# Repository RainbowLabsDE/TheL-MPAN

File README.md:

# TheLÄMPAN
Für so ne Lampe von IKEA ein Custom PCB

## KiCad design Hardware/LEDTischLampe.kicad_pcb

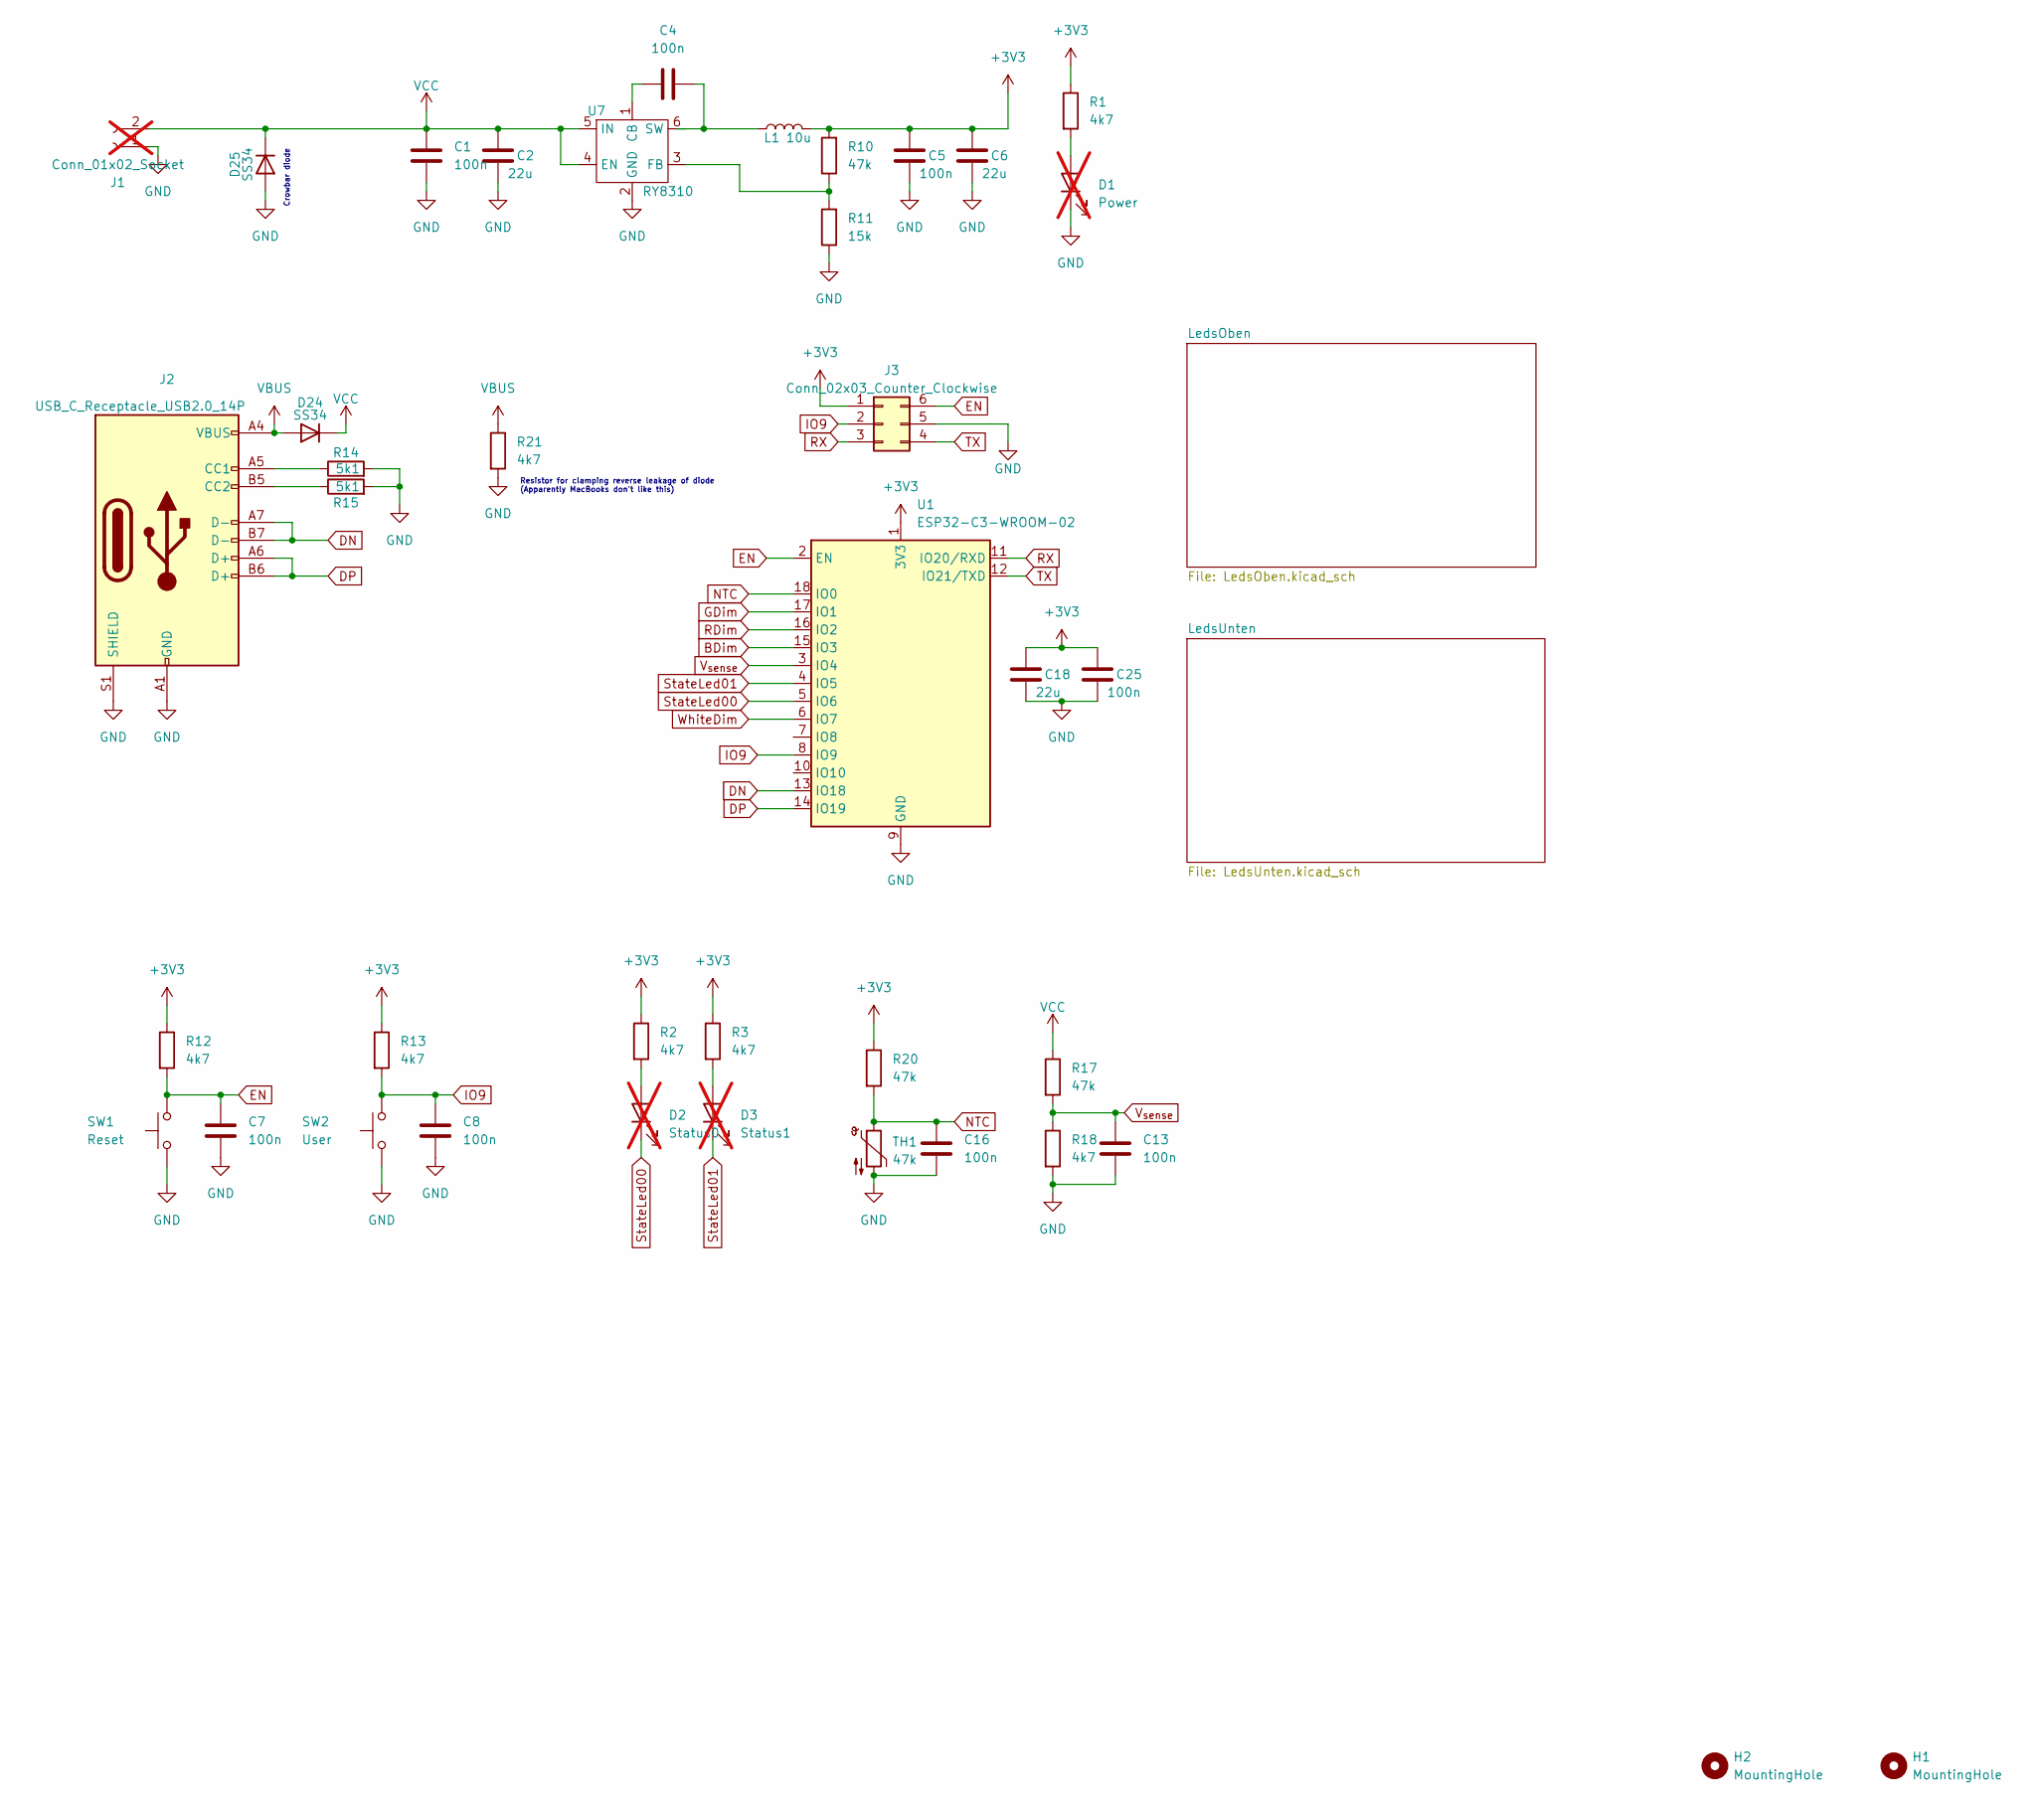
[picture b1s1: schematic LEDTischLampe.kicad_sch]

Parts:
C1, C4, C5, C7, C8, C13, C16, C25: 100n; C_0402_1005Metric
C2, C6, C18: 22u; C_0805_2012Metric
D1: Power; LED_0805_2012Metric; not fitted
D2: Status0; LED_0805_2012Metric; not fitted
D3: Status1; LED_0805_2012Metric; not fitted
D24, D25: SS34; D_SMA
H1, H2: MountingHole; MountingHole_3.2mm_M3
J1: Conn_01x02_Socket; TerminalBlock_Phoenix_PT-1,5-2-5.0-H_1x02_P5.00mm_Horizontal; not fitted
J2: USB_C_Receptacle_USB2.0_14P; USB-C_SMD-TYPE-C-31-M-12
J3: Conn_02x03_Counter_Clockwise; Tag-Connect_TC2030-IDC-NL_2x03_P1.27mm_Vertical
L1: 10u; IND-SMD_L2.5-W2.0
R1, R2, R3, R12, R13, R18, R21: 4k7; R_0402_1005Metric
R10, R17, R20: 47k; R_0402_1005Metric
R11: 15k; R_0402_1005Metric
R14, R15: 5k1; R_0402_1005Metric
SW1: Reset; SW_SPST_TL3342
SW2: User; SW_SPST_TL3342
TH1: 47k; R_0402_1005Metric
U1: ESP32-C3-WROOM-02
U7: RY8310; SOT-23-6

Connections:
+3V3: C5.1, C6.1, C18.1, C25.1, J3.1, L1.2, R1.1, R2.1, R3.1, R10.2, R12.1, R13.1, R20.1, U1.1 (3V3)
BDim: U1.15 (IO3); also elsewhere on the board
DN: J2.A7 (D-), J2.B7 (D-), U1.13 (IO18)
DP: J2.A6 (D+), J2.B6 (D+), U1.14 (IO19)
EN: C7.1, J3.6, R12.2, SW1.2, U1.2 (EN)
GDim: U1.17 (IO1); also elsewhere on the board
GND: C1.2, C2.2, C5.2, C6.2, C7.2, C8.2, C13.2, C16.2, C18.2, C25.2, D1.1 (K), D25.2 (A), J1.1, J2.A1 (GND), J2.A12 (GND), J2.B1 (GND), J2.B12 (GND), J2.S1 (SHIELD), J3.5, R11.1, R14.2, R15.2, R18.2, R21.2, SW1.1, SW2.1, TH1.2, U1.9 (GND), U1.19 (GND), U7.2 (GND); also elsewhere on the board
IO9: C8.1, J3.2, R13.2, SW2.2, U1.8 (IO9)
NTC: C16.1, R20.2, TH1.1, U1.18 (IO0)
unnamed: C4.2, L1.1
unnamed: D1.2 (A), R1.2
unnamed: D2.2 (A), R2.2
unnamed: D3.2 (A), R3.2
unnamed: J2.A5 (CC1), R14.1
unnamed: J2.B5 (CC2), R15.1
unnamed: C4.1, U7.1 (CB)
unnamed: R10.1, R11.2, U7.3 (FB)
RDim: U1.16 (IO2); also elsewhere on the board
RX: J3.3, U1.11 (IO20/RXD)
StateLed00: D2.1 (K), U1.5 (IO6)
StateLed01: D3.1 (K), U1.4 (IO5)
TX: J3.4, U1.12 (IO21/TXD)
VBUS: D24.2 (A), J2.A4 (VBUS), J2.A9 (VBUS), J2.B4 (VBUS), J2.B9 (VBUS), R21.1
VCC: C1.1, C2.1, D24.1 (K), D25.1 (K), J1.2, R17.1, U7.4 (EN), U7.5 (IN); also elsewhere on the board
V_{sense}: C13.1, R17.2, R18.1, U1.3 (IO4)
WhiteDim: U1.6 (IO7); also elsewhere on the board

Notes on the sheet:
Crowbar diode
Resistor for clamping reverse leakage of diode (Apparently MacBooks don't like this)

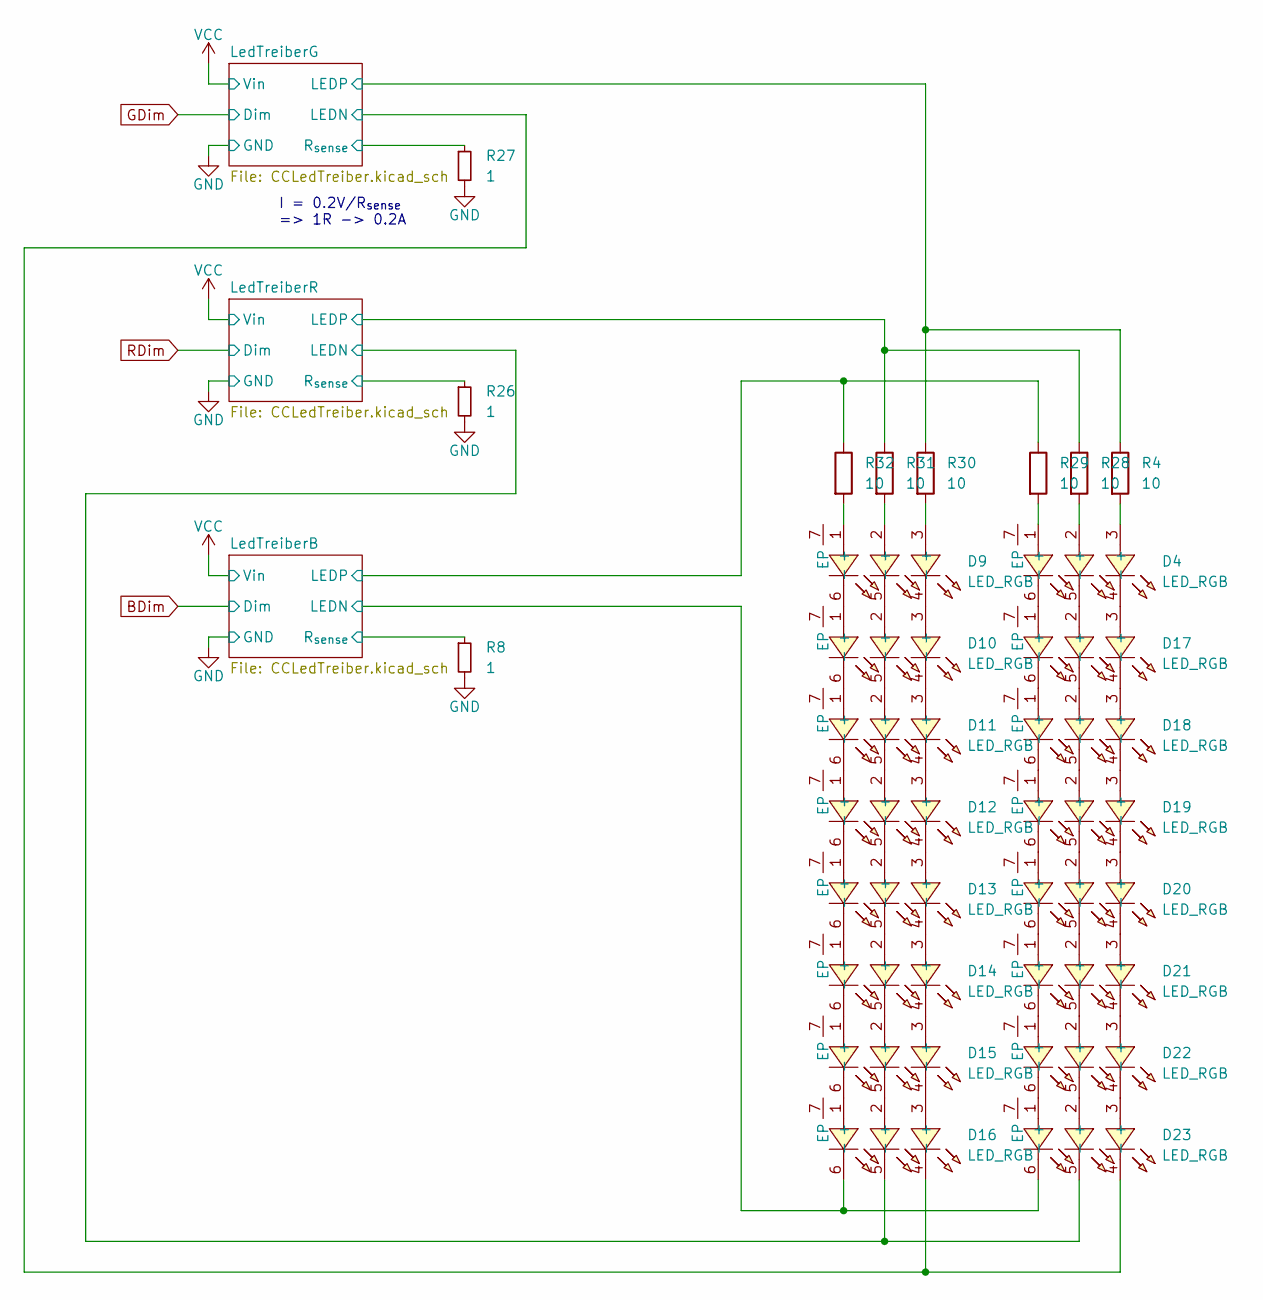
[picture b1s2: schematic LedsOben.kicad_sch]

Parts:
D4, D9, D10, D11, D12, D13, D14, D15, D16, D17, D18, D19, D20, D21, D22, D23: LED_RGB; LED-SMD_6P-L5.0-W5.0-BL_TC5053RGBE60
R4, R28, R29, R30, R31, R32: 10; R_0805_2012Metric
R8, R26, R27: 1; R_0805_2012Metric

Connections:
/LedsOben/LedTreiberB/LEDN: D16.6 (-), D23.6 (-), R8.1; also elsewhere on the board
/LedsOben/LedTreiberB/LEDP: R29.1, R32.1; also elsewhere on the board
/LedsOben/LedTreiberG/LEDN: D16.4 (-), D23.4 (-), R27.1; also elsewhere on the board
/LedsOben/LedTreiberG/LEDP: R4.1, R30.1; also elsewhere on the board
/LedsOben/LedTreiberR/LEDN: D16.5 (-), D23.5 (-), R26.1; also elsewhere on the board
/LedsOben/LedTreiberR/LEDP: R28.1, R31.1; also elsewhere on the board
GND: R8.2, R26.2, R27.2; also elsewhere on the board
unnamed: D4.1 (+), R29.2
unnamed: D4.2 (+), R28.2
unnamed: D4.3 (+), R4.2
unnamed: D9.1 (+), R32.2
unnamed: D9.2 (+), R31.2
unnamed: D9.3 (+), R30.2
unnamed: D9.6 (-), D10.1 (+)
unnamed: D9.5 (-), D10.2 (+)
unnamed: D9.4 (-), D10.3 (+)
unnamed: D10.4 (-), D11.3 (+)
unnamed: D10.5 (-), D11.2 (+)
unnamed: D10.6 (-), D11.1 (+)
unnamed: D11.4 (-), D12.3 (+)
unnamed: D11.5 (-), D12.2 (+)
unnamed: D11.6 (-), D12.1 (+)
unnamed: D12.4 (-), D13.3 (+)
unnamed: D12.5 (-), D13.2 (+)
unnamed: D12.6 (-), D13.1 (+)
unnamed: D13.4 (-), D14.3 (+)
unnamed: D13.5 (-), D14.2 (+)
unnamed: D13.6 (-), D14.1 (+)
unnamed: D14.4 (-), D15.3 (+)
unnamed: D14.5 (-), D15.2 (+)
unnamed: D14.6 (-), D15.1 (+)
unnamed: D15.4 (-), D16.3 (+)
unnamed: D15.5 (-), D16.2 (+)
unnamed: D15.6 (-), D16.1 (+)
unnamed: D4.6 (-), D17.1 (+)
unnamed: D4.5 (-), D17.2 (+)
unnamed: D4.4 (-), D17.3 (+)
unnamed: D17.4 (-), D18.3 (+)
unnamed: D17.5 (-), D18.2 (+)
unnamed: D17.6 (-), D18.1 (+)
unnamed: D18.4 (-), D19.3 (+)
unnamed: D18.5 (-), D19.2 (+)
unnamed: D18.6 (-), D19.1 (+)
unnamed: D19.4 (-), D20.3 (+)
unnamed: D19.5 (-), D20.2 (+)
unnamed: D19.6 (-), D20.1 (+)
unnamed: D20.4 (-), D21.3 (+)
unnamed: D20.5 (-), D21.2 (+)
unnamed: D20.6 (-), D21.1 (+)
unnamed: D21.4 (-), D22.3 (+)
unnamed: D21.5 (-), D22.2 (+)
unnamed: D21.6 (-), D22.1 (+)
unnamed: D22.4 (-), D23.3 (+)
unnamed: D22.5 (-), D23.2 (+)
unnamed: D22.6 (-), D23.1 (+)

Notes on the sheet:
I = 0.2V/R_{sense} => 1R -> 0.2A

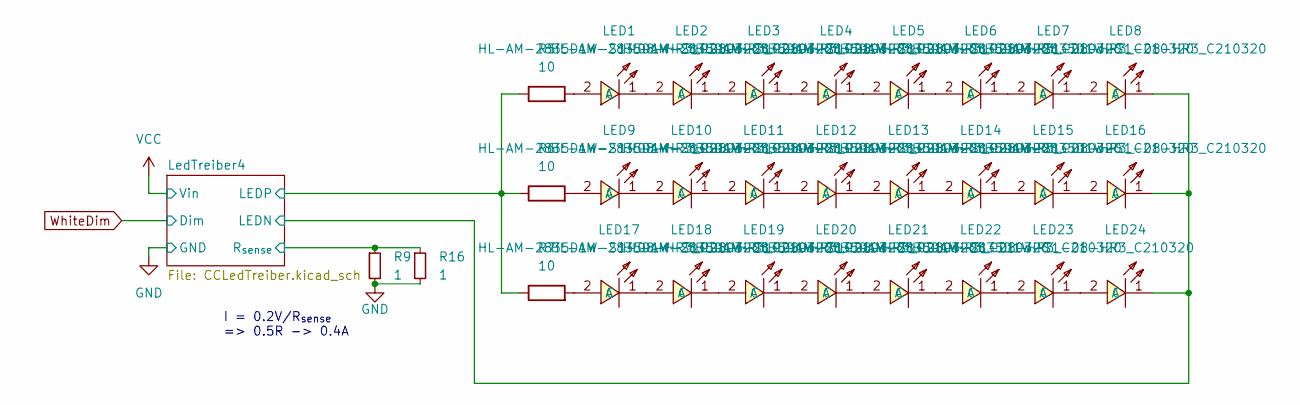
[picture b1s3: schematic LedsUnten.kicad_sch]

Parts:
LED1, LED2, LED3, LED4, LED5, LED6, LED7, LED8, LED9, LED10, LED11, LED12, LED13, LED14, LED15, LED16, LED17, LED18, LED19, LED20, LED21, LED22, LED23, LED24: HL-AM-2835D1W-S1-08-HR3_C210320; LED-SMD_L3.3-W2.8-RD
R5, R6, R7: 10; R_0805_2012Metric
R9, R16: 1; R_0805_2012Metric

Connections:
/LedsUnten/LedTreiber4/LEDN: LED8.1 (C), LED16.1 (C), LED24.1 (C), R9.1, R16.1; also elsewhere on the board
/LedsUnten/LedTreiber4/LEDP: R5.1, R6.1, R7.1; also elsewhere on the board
GND: R9.2, R16.2; also elsewhere on the board
unnamed: LED1.2 (A), R5.2
unnamed: LED1.1 (C), LED2.2 (A)
unnamed: LED2.1 (C), LED3.2 (A)
unnamed: LED3.1 (C), LED4.2 (A)
unnamed: LED4.1 (C), LED5.2 (A)
unnamed: LED5.1 (C), LED6.2 (A)
unnamed: LED6.1 (C), LED7.2 (A)
unnamed: LED7.1 (C), LED8.2 (A)
unnamed: LED9.2 (A), R6.2
unnamed: LED9.1 (C), LED10.2 (A)
unnamed: LED10.1 (C), LED11.2 (A)
unnamed: LED11.1 (C), LED12.2 (A)
unnamed: LED12.1 (C), LED13.2 (A)
unnamed: LED13.1 (C), LED14.2 (A)
unnamed: LED14.1 (C), LED15.2 (A)
unnamed: LED15.1 (C), LED16.2 (A)
unnamed: LED17.2 (A), R7.2
unnamed: LED17.1 (C), LED18.2 (A)
unnamed: LED18.1 (C), LED19.2 (A)
unnamed: LED19.1 (C), LED20.2 (A)
unnamed: LED20.1 (C), LED21.2 (A)
unnamed: LED21.1 (C), LED22.2 (A)
unnamed: LED22.1 (C), LED23.2 (A)
unnamed: LED23.1 (C), LED24.2 (A)

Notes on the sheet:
I = 0.2V/R_{sense} => 0.5R -> 0.4A

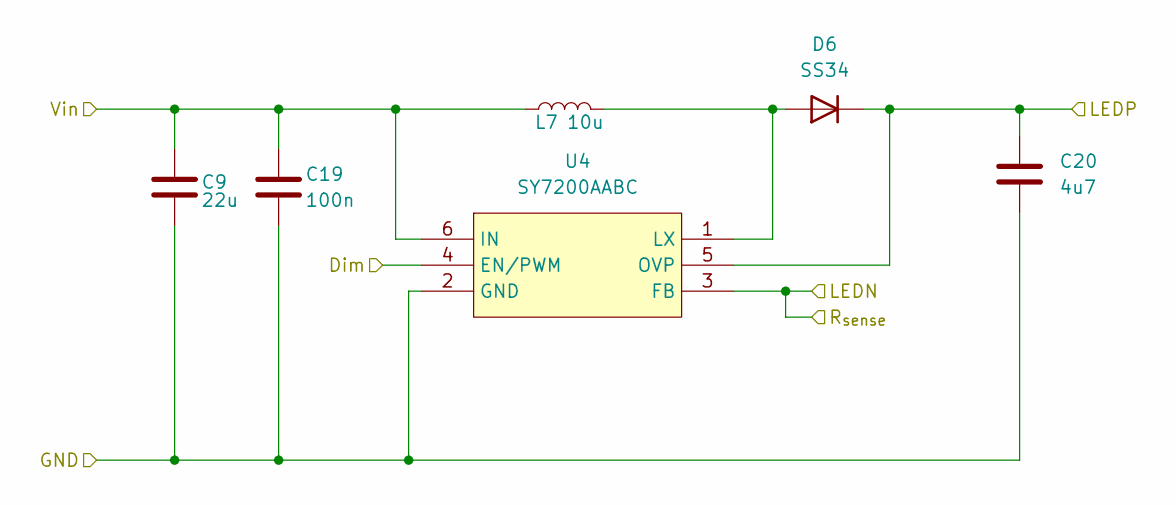
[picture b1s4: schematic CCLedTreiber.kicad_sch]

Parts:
C9: 22u; C_0805_2012Metric
C19: 100n; C_0402_1005Metric
C20: 4u7; C_1206_3216Metric
D6: SS34; D_SMA
L7: 10u; IND-SMD_L2.5-W2.0
U4: SY7200AABC; SOT-23-6_L2.9-W1.6-P0.95-LS2.8-BR

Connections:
/LedsOben/LedTreiberB/LEDN: U4.3 (FB); also elsewhere on the board
/LedsOben/LedTreiberB/LEDP: C20.1, D6.1 (K), U4.5 (OVP); also elsewhere on the board
BDim: U4.4 (EN/PWM); also elsewhere on the board
GND: C9.2, C19.2, C20.2, U4.2 (GND); also elsewhere on the board
unnamed: D6.2 (A), L7.2, U4.1 (LX)
VCC: C9.1, C19.1, L7.1, U4.6 (IN); also elsewhere on the board

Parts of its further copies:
C3, C21, C23: 100n; C_0402_1005Metric
C10, C11, C12: 22u; C_0805_2012Metric
C17, C22, C24: 4u7; C_1206_3216Metric
D5, D7, D8: SS34; D_SMA
L8, L9, L10: 10u; IND-SMD_L2.5-W2.0
U3, U5, U6: SY7200AABC; SOT-23-6_L2.9-W1.6-P0.95-LS2.8-BR

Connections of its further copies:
/LedsOben/LedTreiberG/LEDN: U6.3 (FB); also elsewhere on the board
/LedsOben/LedTreiberG/LEDP: C24.1, D8.1 (K), U6.5 (OVP); also elsewhere on the board
/LedsOben/LedTreiberR/LEDN: U5.3 (FB); also elsewhere on the board
/LedsOben/LedTreiberR/LEDP: C22.1, D7.1 (K), U5.5 (OVP); also elsewhere on the board
/LedsUnten/LedTreiber4/LEDN: U3.3 (FB); also elsewhere on the board
/LedsUnten/LedTreiber4/LEDP: C17.1, D5.1 (K), U3.5 (OVP); also elsewhere on the board
GDim: U6.4 (EN/PWM); also elsewhere on the board
GND: C3.2, C10.2, C11.2, C12.2, C17.2, C21.2, C22.2, C23.2, C24.2, U3.2 (GND), U5.2 (GND), U6.2 (GND); also elsewhere on the board
unnamed: D5.2 (A), L8.2, U3.1 (LX)
unnamed: D7.2 (A), L9.2, U5.1 (LX)
unnamed: D8.2 (A), L10.2, U6.1 (LX)
RDim: U5.4 (EN/PWM); also elsewhere on the board
VCC: C3.1, C10.1, C11.1, C12.1, C21.1, C23.1, L8.1, L9.1, L10.1, U3.6 (IN), U5.6 (IN), U6.6 (IN); also elsewhere on the board
WhiteDim: U3.4 (EN/PWM); also elsewhere on the board

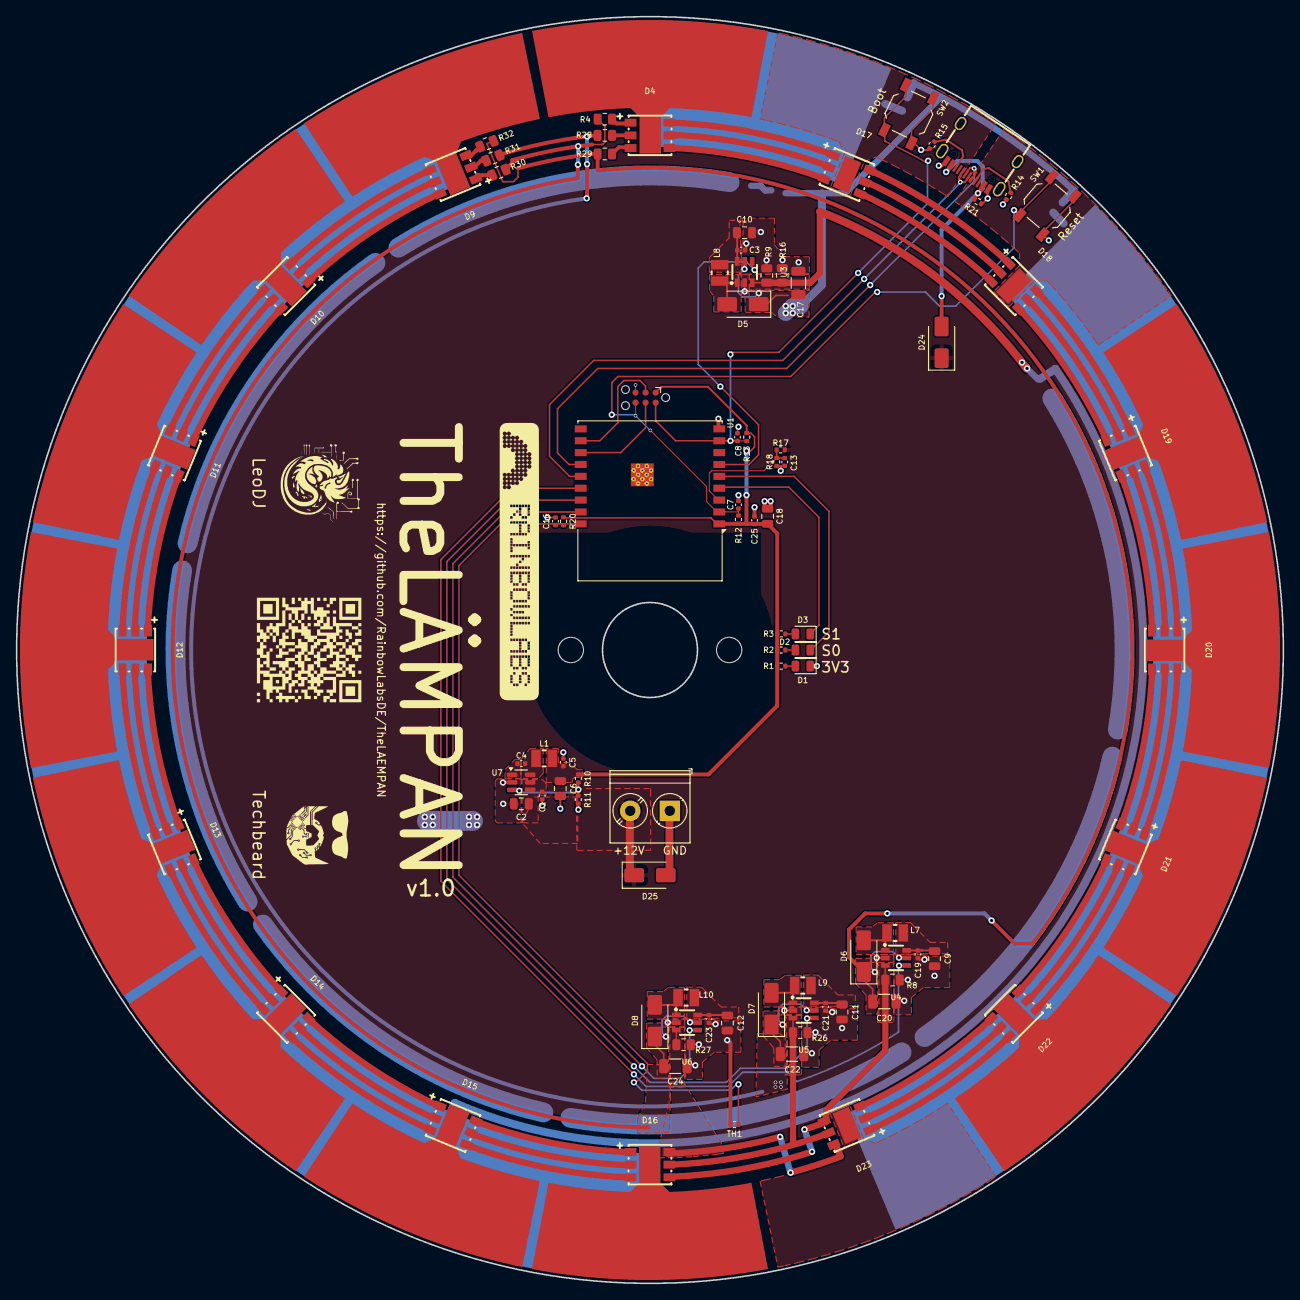
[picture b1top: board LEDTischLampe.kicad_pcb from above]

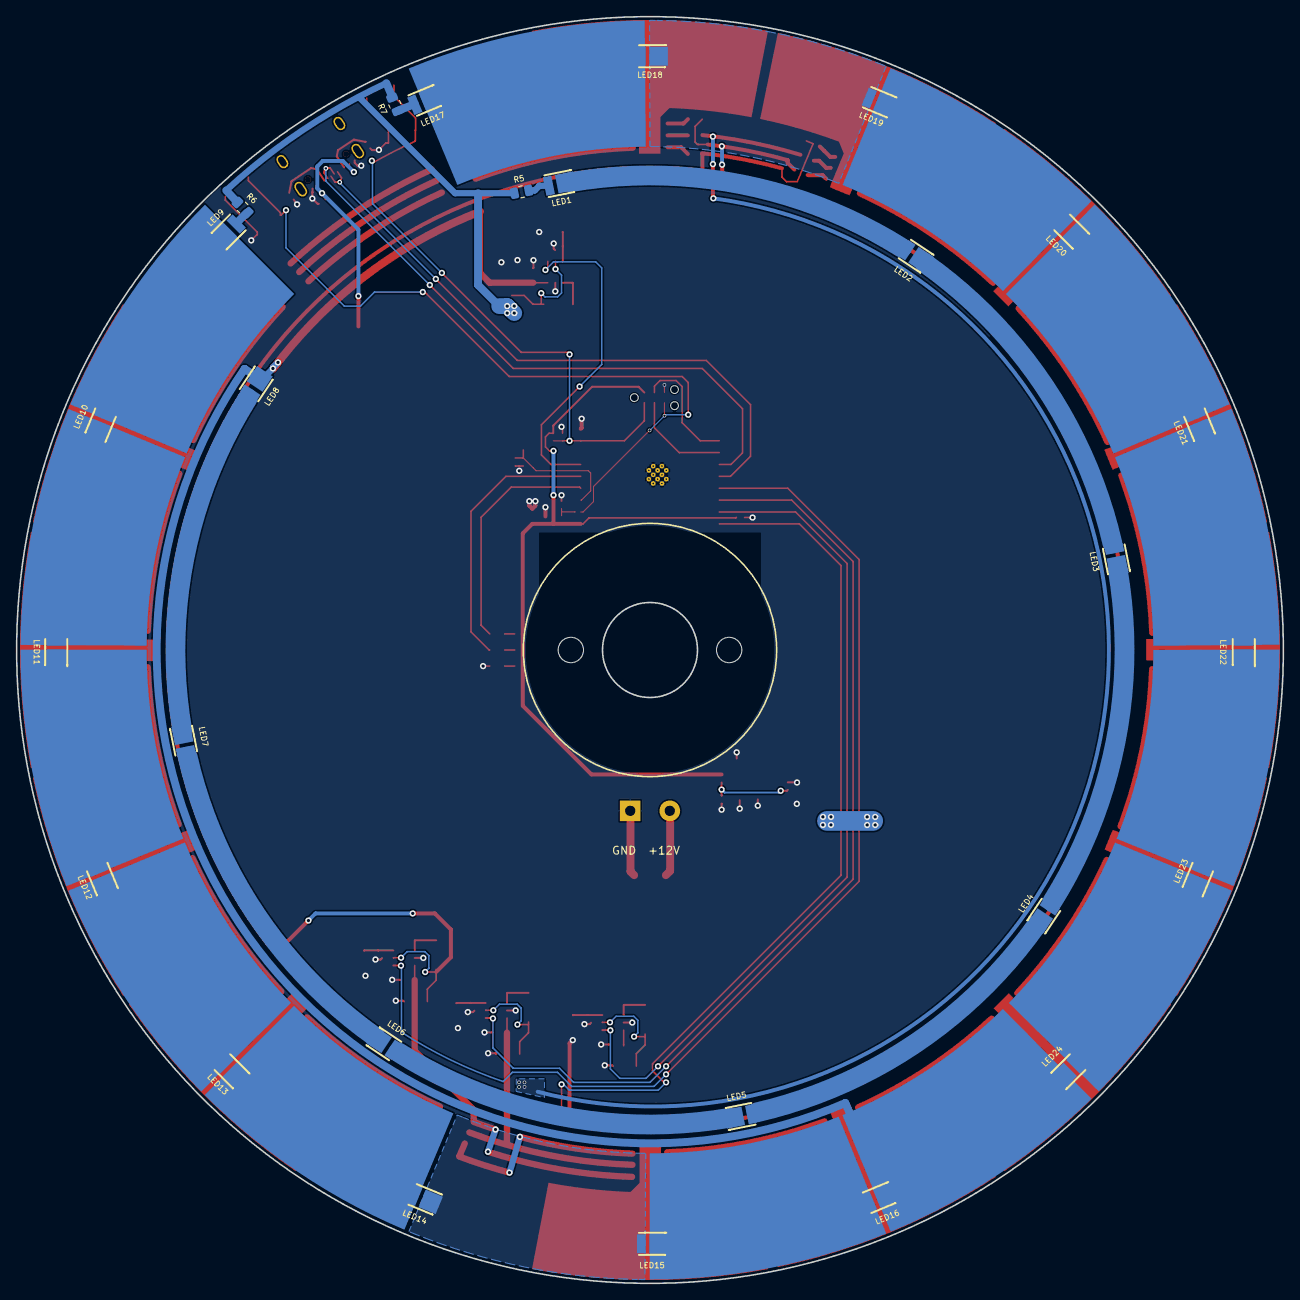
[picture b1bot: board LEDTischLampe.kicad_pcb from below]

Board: 2 copper layers, 160.0 x 160.0 mm, 118 parts (27 on the bottom side), 110 nets.

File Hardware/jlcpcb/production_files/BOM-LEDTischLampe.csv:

Comment,Designator,Footprint,LCSC
SY7200AABC,"U3,U4,U5,U6",SOT-23-6_L2.9-W1.6-P0.95-LS2.8-BR,C107309
10,"R28,R29,R30,R31,R32,R4,R5,R6,R7",R_0805_2012Metric,C17415
HL-AM-2835D1W-S1-08-HR3_C210320,"LED1,LED10,LED11,LED12,LED13,LED14,LED15,LED16,LED17,LED18,LED19,LED2,LED20,LED21,LED22,LED23,LED24,LED3,LED4,LED5,LED6,LED7,LED8,LED9",LED-SMD_L3.3-W2.8-RD,C210320
1,"R16,R26,R27,R8,R9",R_0805_2012Metric,C25271
15k,R11,R_0402_1005Metric,C25756
47k,"R10,R17",R_0402_1005Metric,C25792
4k7,"R1,R12,R13,R18,R2,R20,R21,R3",R_0402_1005Metric,C25900
5k1,"R14,R15",R_0402_1005Metric,C25905
USB_C_Receptacle_USB2.0_14P,J2,USB-C_SMD-TYPE-C-31-M-12,C2927038
ESP32-C3-WROOM-02,U1,ESP32-C3-WROOM-02,C2934560
4u7,"C17,C20,C22,C24",C_1206_3216Metric,C29823
47k,TH1,R_0402_1005Metric,C2991699
100n,"C1,C13,C16,C19,C21,C23,C25,C3,C4,C5,C7,C8",C_0402_1005Metric,C307331
Reset,"SW1,SW2",SW_SPST_TL3342,C318884
RY8310,U7,SOT-23-6,C370876
22u,"C10,C11,C12,C18,C2,C6,C9",C_0805_2012Metric,C45783
10u,"L1,L10,L7,L8,L9",IND-SMD_L2.5-W2.0,C5832376
LED_RGB,"D10,D11,D12,D13,D14,D15,D16,D17,D18,D19,D20,D21,D22,D23,D4,D9",LED-SMD_6P-L5.0-W5.0-BL_TC5053RGBE60,C784542
SS34,"D24,D25,D5,D6,D7,D8",D_SMA,C8678

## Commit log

2024-10-06 Add Files
2024-10-09 edit layout
2024-10-09 a bit more layouting
2024-10-09 finished preliminary routing
2024-10-09 assign most LCSC numbers
2024-10-09 assign remaining LCSC numbers and change R_sense of LED drivers
2024-10-09 remove LCSC numbers from silkscreen (bug in jlcpcb-tools)
2024-10-09 generate new gerbers
2024-10-10 some fixes and BOM optimization, heatsinking, etc
2024-10-10 silkscreen and stuff
2024-10-11 final touches for v1.0
2024-10-11 some more tweaks (rotated input terminal block, added voltage measurement)
2024-10-23 add super basic test firmware
2024-10-23 update RGB mapping in KiCad
2024-10-31 hack in gamma for test firmware
